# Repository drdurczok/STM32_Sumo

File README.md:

# STM32_Sumo
Sumo robot PCB based on STM32 and source code.

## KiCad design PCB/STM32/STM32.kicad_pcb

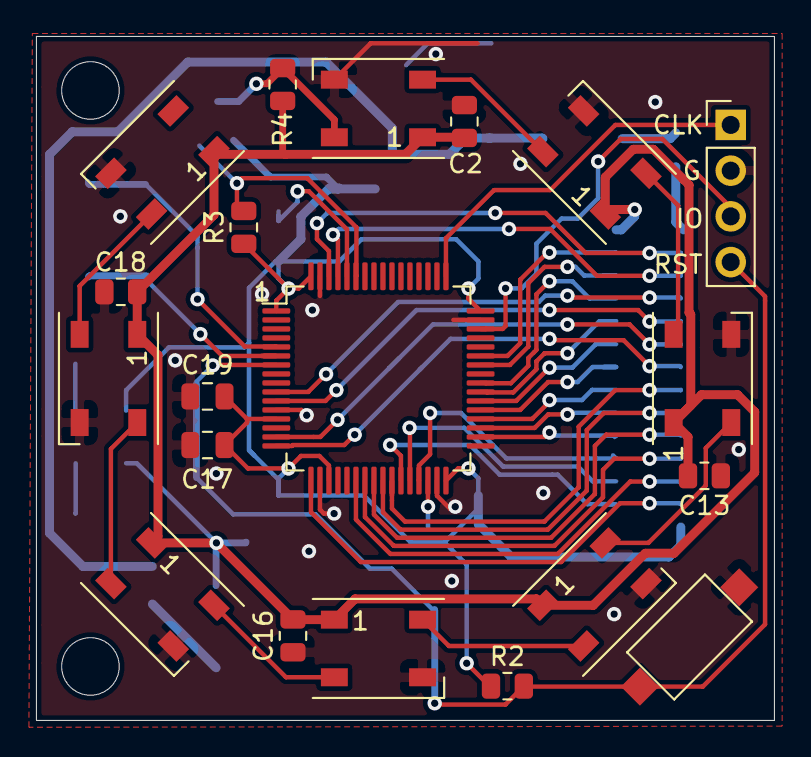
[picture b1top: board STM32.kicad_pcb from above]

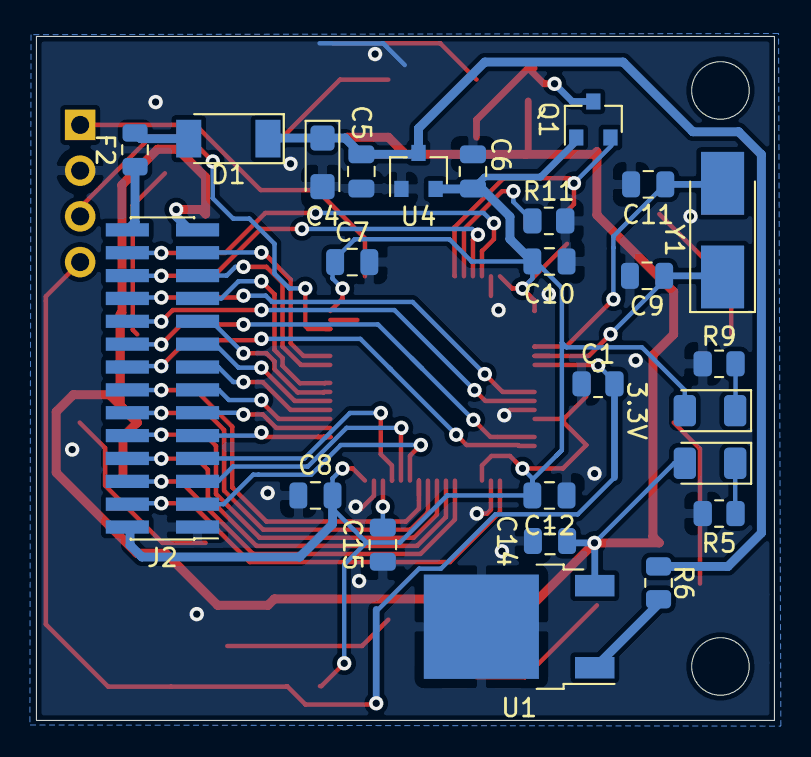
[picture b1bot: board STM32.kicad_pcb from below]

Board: 2 copper layers, 41.0 x 38.0 mm, 45 parts (25 on the bottom side), 49 nets.

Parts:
C1, C2, C13, C16, C18: 100nF; R_0805_2012Metric
C4: 10uF; CP_EIA-3216-18_Kemet-A
C5, C6: 4.7uF; C_0805_2012Metric
C7, C8, C10, C12, C14, C19: 100nF; C_0805_2012Metric
C9, C11: 20pF; C_0805_2012Metric
C15: 2.2uF; C_0805_2012Metric
C17: 1uF; C_0805_2012Metric
D1: Schottky; D_SOD-128
D2, D11: Power_On; LED_1206_3216Metric
D3, D4, D5, D6, D7, D8, D9, D10: WS2812B; LED_WS2812B_PLCC4_5.0x5.0mm_P3.2mm
F2: Fuse; Fuse_0805_2012Metric
J2: St-Link; PinHeader_2x14_P1.27mm_Vertical_SMD
J18: St-Link; PinHeader_1x04_P2.54mm_Vertical
Q1: BSS138; SOT-23
R2: 100k; R_0805_2012Metric
R3, R4: 10K; R_0805_2012Metric
R5, R9: RLed; R_0805_2012Metric
R6: 0R; R_0805_2012Metric
R11: 100K; R_0805_2012Metric
SW1: SW_Push; SW_SPST_CK_RS282G05A3
U1: L7805; TO-252-2
U3: STM32F411RETx; LQFP-64_10x10mm_P0.5mm
U4: MCP1703A-3302_SOT23; SOT-23
Y1: 16MHz; Crystal_SMD_5032-2Pin_5.0x3.2mm_HandSoldering

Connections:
+3V3: C6.1, C7.2, C8.2, C10.1, C12.2, C17.2, C19.1, D2.2, J2.2, Q1.1, R2.1, R3.1, U3.1, U3.13, U3.19, U3.32, U3.48, U3.64, U4.2
+5V: C2.2, C13.2, C14.1, C16.2, C18.2, D3.1, D4.1, D5.1, D6.1, D7.1, D8.1, D9.1, D10.1, D11.2, J2.27, R4.2, U1.3
GND: C1.1, C2.1, C4.2, C5.2, C6.2, C7.1, C8.1, C9.2, C10.2, C11.2, C12.1, C13.1, C14.2, C15.1, C16.1, C17.1, C18.1, C19.2, D3.3, D4.3, D5.3, D6.3, D7.3, D8.3, D9.3, D10.3, J2.1, J18.2, R5.2, R9.2, R11.1, SW1.2, U1.2, U3.12, U3.18, U3.31, U3.47, U3.63, U4.1
LED: D3.4, Q1.3, R4.1
unnamed: C9.1, U3.6, Y1.1
unnamed: C11.1, U3.5, Y1.2
unnamed: C15.2, U3.30
unnamed: D1.2, F2.2
unnamed: D2.1, R9.1
unnamed: D3.2, D4.4
unnamed: D4.2, D5.4
unnamed: D5.2, D6.4
unnamed: D6.2, D7.4
unnamed: D7.2, D8.4
unnamed: D8.2, D9.4
unnamed: D9.2, D10.4
unnamed: D11.1, R5.1
unnamed: R6.1, U1.1
unnamed: R11.2, U3.60
PA1: J2.18, U3.15
PA2: J2.16, U3.16
PA3: J2.4, U3.17
PA6: J2.6, U3.22
PA7: J2.8, U3.23
PA9: J2.23, U3.42
PA10: J2.25, U3.43
PB0: J2.14, U3.26
PB1: J2.3, U3.27
PB2: J2.5, U3.28
PB7: Q1.2, R3.2, U3.59
PB8: J2.24, U3.61
PB9: J2.26, U3.62
PB10: J2.7, U3.29
PB13: J2.9, U3.34
PB14: J2.11, U3.35
PB15: J2.13, U3.36
PC2: J2.22, U3.10
PC3: J2.20, U3.11
PC4: J2.10, U3.24
PC5: J2.12, U3.25
PC6: J2.15, U3.37
PC7: J2.17, U3.38
PC8: J2.19, U3.39
PC9: J2.21, U3.40
RESET: C1.2, J18.4, R2.2, SW1.1, U3.7
SWD_CLK: J18.1, U3.49
SWD_IO: J18.3, U3.46
VPP: F2.1, J2.28
V_Stable: C4.1, C5.1, D1.1, R6.2, U4.3

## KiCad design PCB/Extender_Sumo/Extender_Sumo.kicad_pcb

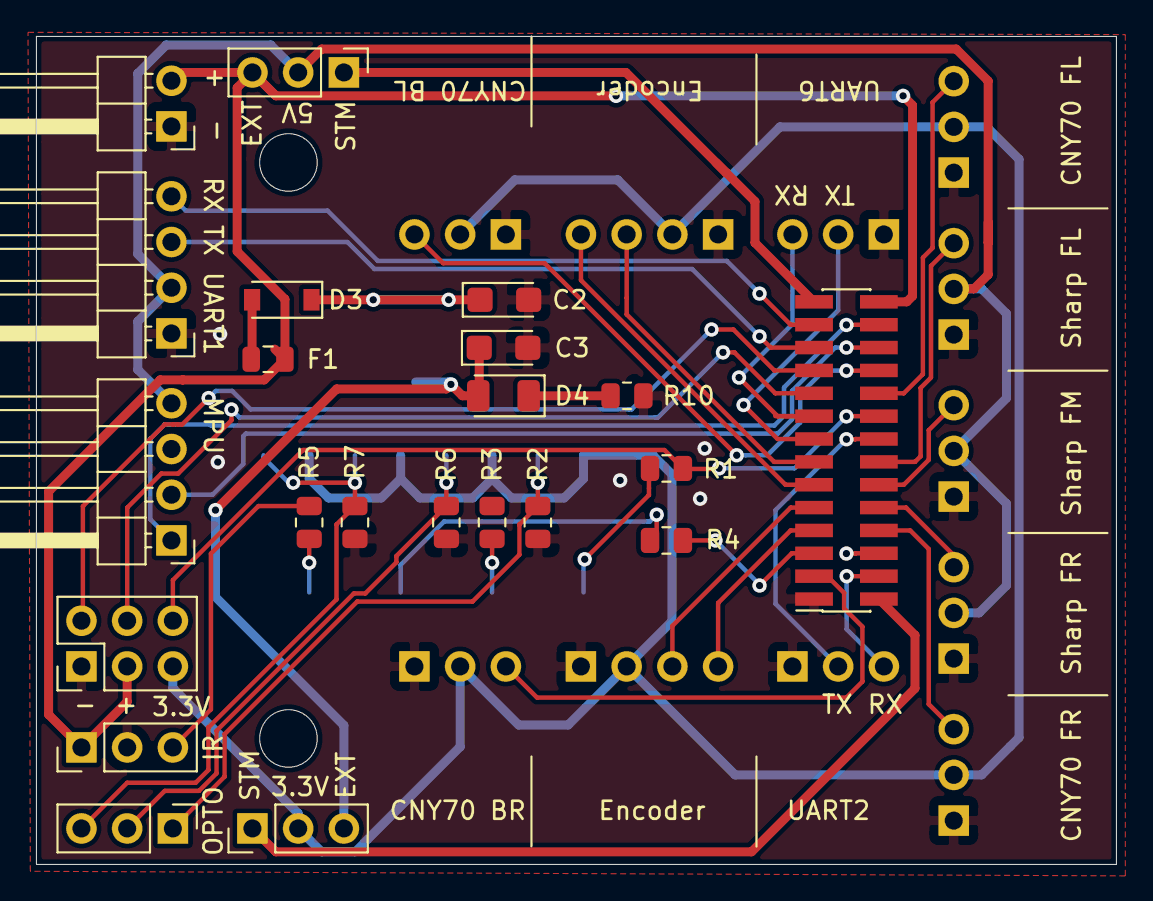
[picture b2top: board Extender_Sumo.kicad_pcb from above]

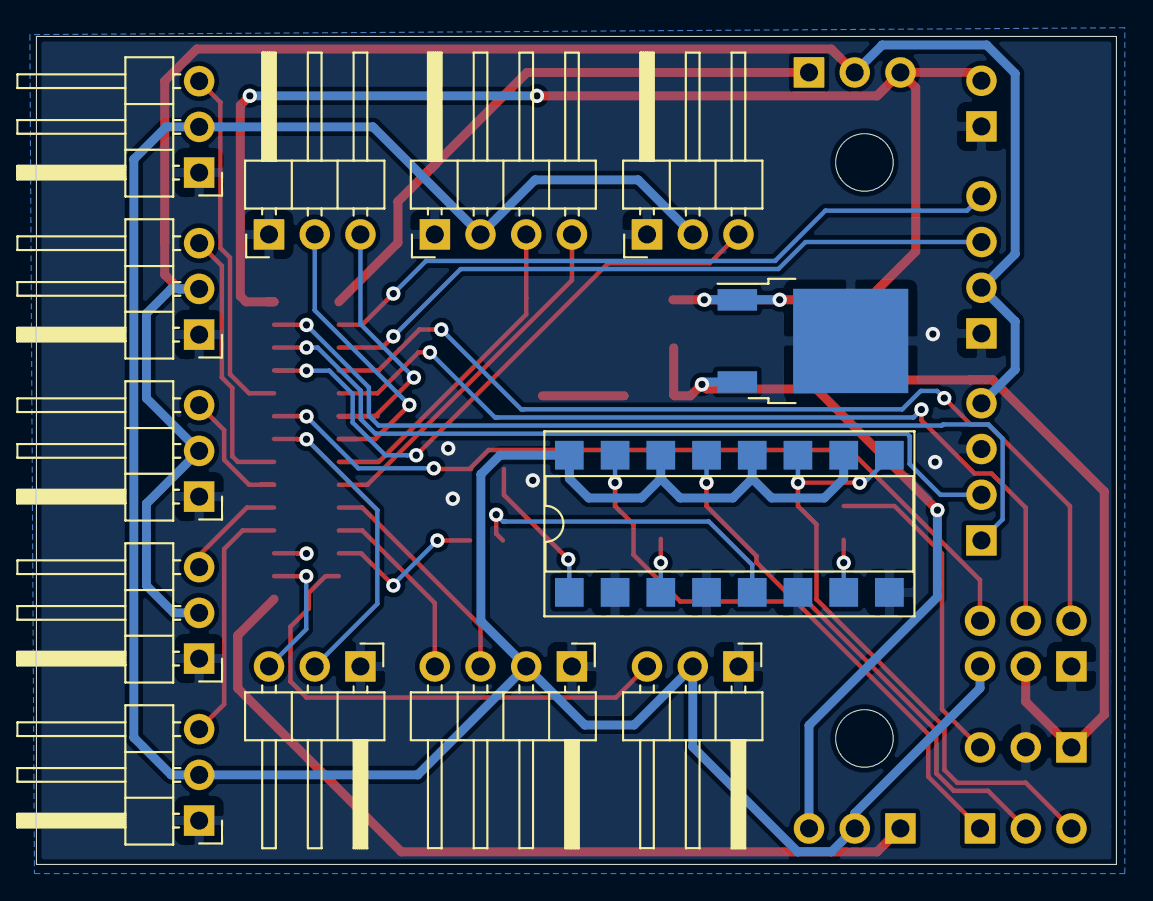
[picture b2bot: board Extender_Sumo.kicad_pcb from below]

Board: 2 copper layers, 60.0 x 46.0 mm, 35 parts (13 on the bottom side), 41 nets.

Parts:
C2, C3: 10uf; CP_EIA-3216-18_Kemet-A
D3: Schottky; D_SOD-123
D4: Power_On; LED_1206_3216Metric
F1: Fuse; Fuse_0805_2012Metric
J1: CNY70 FR; PinHeader_1x03_P2.54mm_Horizontal
J2: CNY70 FL; PinHeader_1x03_P2.54mm_Horizontal
J3: Sharp FL; PinHeader_1x03_P2.54mm_Horizontal
J4: Sharp FM; PinHeader_1x03_P2.54mm_Horizontal
J5: Sharp FR; PinHeader_1x03_P2.54mm_Horizontal
J6: Right Driver; PinHeader_1x03_P2.54mm_Horizontal
J7: Left Driver; PinHeader_1x03_P2.54mm_Horizontal
J8: Right Encoder; PinHeader_1x04_P2.54mm_Horizontal
J9: CNY70 BR; PinHeader_1x03_P2.54mm_Horizontal
J10: CNY70 BL; PinHeader_1x03_P2.54mm_Horizontal
J11: Left Encoder; PinHeader_1x04_P2.54mm_Horizontal
J12: Extra Pins; PinHeader_2x03_P2.54mm_Vertical
J13: Conn_02x14_Odd_Even; PinSocket_2x14_P1.27mm_Vertical_SMD
J14: IR Module; PinHeader_1x03_P2.54mm_Vertical
J15: Bluetooth; PinHeader_1x04_P2.54mm_Horizontal
J16: Optocoupler Out; PinHeader_1x03_P2.54mm_Vertical
J17: MPU6050 I2C; PinHeader_1x04_P2.54mm_Horizontal
J18, J19: Conn_01x03; PinHeader_1x03_P2.54mm_Vertical
J20: Conn_01x02; PinHeader_1x02_P2.54mm_Horizontal
R1, R3, R4, R5: 330R; R_0805_2012Metric
R2, R6, R7: 10K; R_0805_2012Metric
R10: RLed; R_0805_2012Metric
U1: LF33_TO252; TO-252-2
U2: LTV-847; DIP-16_W7.62mm_SMDSocket_SmallPads

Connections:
3.3V_1A: C3.1, D4.2, J18.3, U1.3
3.3V_STM: J13.2, J18.1
5V_STM: J13.27, J19.1
+3V3: J1.2, J2.2, J8.2, J9.2, J10.2, J11.2, J12.5, J18.2, U2.10, U2.12, U2.14, U2.16
+5V: J3.2, J4.2, J5.2, J15.2, J17.4, J19.2
GND: C2.2, C3.2, J1.1, J2.1, J3.1, J4.1, J5.1, J6.1, J7.1, J8.1, J9.1, J10.1, J11.1, J12.1, J13.1, J14.2, J15.1, J17.3, J20.1, R2.2, R6.2, R7.2, R10.1, U1.2, U2.2, U2.4, U2.6, U2.8
unnamed: C2.1, D3.1, U1.1
unnamed: D3.2, F1.2
unnamed: D4.1, R10.2
unnamed: J14.3, R5.2
unnamed: J16.1, R2.1, U2.15
unnamed: J16.2, R6.1, U2.13
unnamed: J16.3, R7.1, U2.9, U2.11
unnamed: R1.1, U2.1
unnamed: R3.1, U2.3
unnamed: R4.1, U2.5
unnamed: R5.1, U2.7
PA1: J12.6, J13.18, R1.2
PA2: J6.2, J13.16
PA3: J6.3, J13.4
PA7: J1.3, J13.8
PA9: J13.23, J15.3
PA10: J13.25, J15.4
PB0: J3.3, J13.14
PB1: J9.3, J13.3
PB2: J13.5, R4.2
PB8: J13.24, J17.2
PB9: J13.26, J17.1
PB10: J8.4, J13.7
PB13: J8.3, J13.9
PB14: J11.4, J13.11
PB15: J11.3, J13.13
PC2: J10.3, J13.22
PC3: J2.3, J13.20
PC4: J5.3, J13.10
PC5: J4.3, J13.12
PC6: J7.2, J13.15
PC7: J7.3, J13.17
PC8: J12.4, J13.19
PC9: J12.2, J13.21
VPP: F1.1, J12.3, J13.28, J14.1, J19.3, J20.2

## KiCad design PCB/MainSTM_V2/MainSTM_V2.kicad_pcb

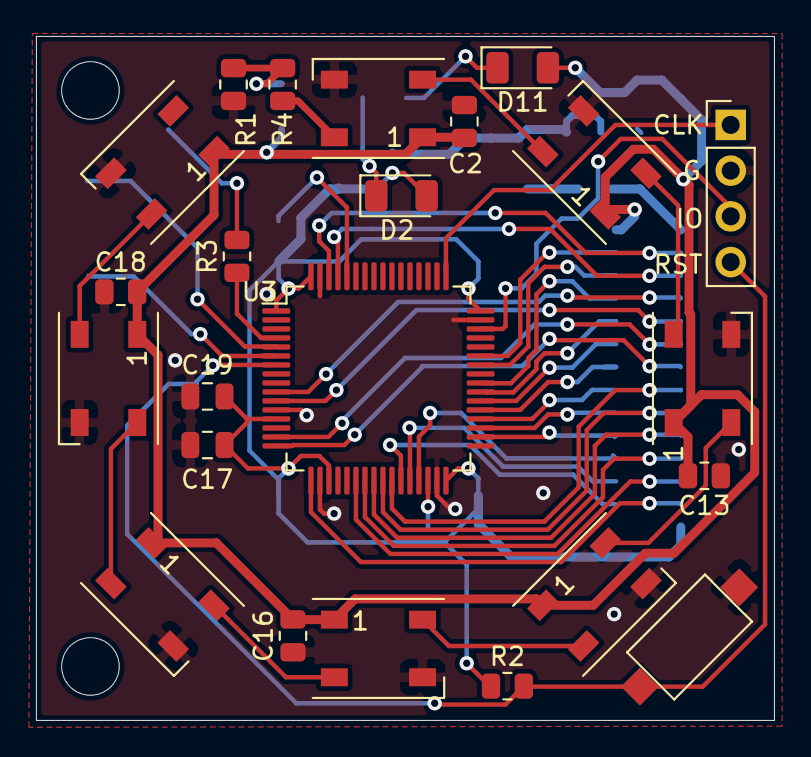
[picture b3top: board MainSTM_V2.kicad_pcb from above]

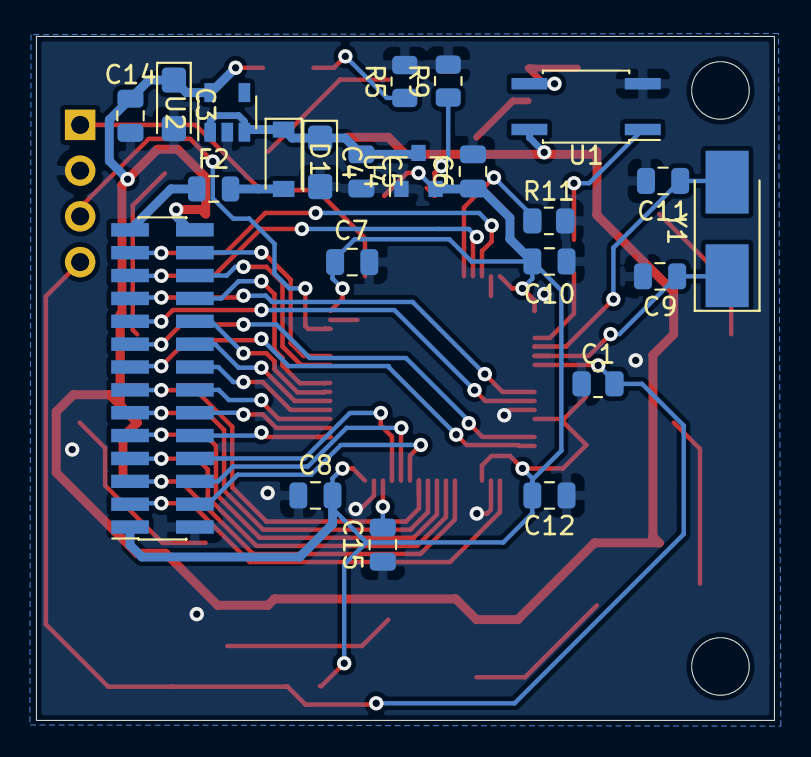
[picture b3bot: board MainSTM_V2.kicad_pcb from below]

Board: 2 copper layers, 41.0 x 38.0 mm, 46 parts (23 on the bottom side), 50 nets.

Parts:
C1, C2, C13, C16, C18: 100nF; R_0805_2012Metric
C3, C4: 10uF; CP_EIA-3216-18_Kemet-A
C5, C6: 4.7uF; C_0805_2012Metric
C7, C8, C10, C12, C14, C19: 100nF; C_0805_2012Metric
C9, C11: 20pF; C_0805_2012Metric
C15: 2.2uF; C_0805_2012Metric
C17: 1uF; C_0805_2012Metric
CLK: St-Link; PinHeader_1x04_P2.54mm_Vertical
D1: Schottky; D_SOD-123
D2, D11: Power_On; LED_1206_3216Metric
D3, D4, D5, D6, D7, D8, D9, D10: WS2812B; LED_WS2812B_PLCC4_5.0x5.0mm_P3.2mm
F2: Fuse; Fuse_0805_2012Metric
J2: St-Link; PinSocket_2x14_P1.27mm_Vertical_SMD
R1: 10k; R_0805_2012Metric
R2: 100k; R_0805_2012Metric
R3: 220R; R_0805_2012Metric
R4: 0R; R_0805_2012Metric
R5, R9: RLed; R_0805_2012Metric
R11: 100K; R_0805_2012Metric
SW1: SW_Push; SW_SPST_CK_RS282G05A3
U1: LTV-356T; SO-4_4.4x3.6mm_P2.54mm
U2: MIC5205-5.0YM5; SOT-23-5
U3: STM32F411RETx; LQFP-64_10x10mm_P0.5mm
U4: MCP1703A-3302_SOT23; SOT-23
Y1: 16MHz; Crystal_SMD_5032-2Pin_5.0x3.2mm_HandSoldering

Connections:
+3V3: C6.1, C7.2, C8.2, C10.1, C12.2, C17.2, C19.1, D2.2, J2.1, R2.1, U3.1, U3.13, U3.19, U3.32, U3.48, U3.64, U4.2
+5V: C2.2, C3.1, C13.2, C14.1, C16.2, C18.2, D3.1, D4.1, D5.1, D6.1, D7.1, D8.1, D9.1, D10.1, D11.2, J2.28, U1.4, U2.5
GND: C1.1, C2.1, C3.2, C4.2, C5.2, C6.2, C7.1, C8.1, C9.2, C10.2, C11.2, C12.1, C13.1, C14.2, C15.1, C16.1, C17.1, C18.1, C19.2, CLK.2, D3.3, D4.3, D5.3, D6.3, D7.3, D8.3, D9.3, D10.3, J2.2, R1.2, R5.2, R9.2, R11.1, SW1.2, U1.2, U2.2, U3.12, U3.18, U3.31, U3.47, U3.63, U4.1
LED: D3.4, R4.2
unnamed: C9.1, U3.6, Y1.1
unnamed: C11.1, U3.5, Y1.2
unnamed: C15.2, U3.30
unnamed: D1.2, F2.2
unnamed: D2.1, R9.1
unnamed: D3.2, D4.4
unnamed: D4.2, D5.4
unnamed: D5.2, D6.4
unnamed: D6.2, D7.4
unnamed: D7.2, D8.4
unnamed: D8.2, D9.4
unnamed: D9.2, D10.4
unnamed: D11.1, R5.1
unnamed: R1.1, R4.1, U1.3
unnamed: R3.2, U1.1
unnamed: R11.2, U3.60
PA1: J2.17, U3.15
PA2: J2.15, U3.16
PA3: J2.3, U3.17
PA6: J2.5, U3.22
PA7: J2.7, U3.23
PA9: J2.24, U3.42
PA10: J2.26, U3.43
PB0: J2.13, U3.26
PB1: J2.4, U3.27
PB2: J2.6, U3.28
PB8: J2.23, U3.61
PB9: J2.25, U3.62
PB10: J2.8, U3.29
PB13: J2.10, U3.34
PB14: J2.12, U3.35
PB15: J2.14, U3.36
PC2: J2.21, U3.10
PC3: J2.19, U3.11
PC4: J2.9, U3.24
PC5: J2.11, U3.25
PC6: J2.16, U3.37
PC7: J2.18, U3.38
PC8: J2.20, U3.39
PC9: J2.22, U3.40
PC15: R3.1, U3.4
RESET: C1.2, CLK.4, R2.2, SW1.1, U3.7
SWD_CLK: CLK.1, U3.49
SWD_IO: CLK.3, U3.46
VPP: F2.1, J2.27
V_Stable: C4.1, C5.1, D1.1, U2.1, U2.3, U4.3

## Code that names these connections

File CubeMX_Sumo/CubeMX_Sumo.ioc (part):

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Mcu.Name=STM32F411R(C-E)Tx
Mcu.Package=LQFP64
Mcu.UserName=STM32F411RETx
PA10.Mode=Asynchronous
PA10.Signal=USART1_RX
PA2.Mode=Asynchronous
PA2.Signal=USART2_TX
PA3.Mode=Asynchronous
PA3.Signal=USART2_RX
PA6.GPIOParameters=GPIO_Label
PA6.GPIO_Label=Sharp RM
PA6.Signal=ADCx_IN6
PA7.GPIOParameters=GPIO_Label
PA7.GPIO_Label=CNY70 FR
PA7.Signal=ADCx_IN7
PA9.Mode=Asynchronous
PA9.Signal=USART1_TX
PB0.GPIOParameters=GPIO_Label
PB0.GPIO_Label=Sharp FL
PB0.Signal=ADCx_IN8
PB1.GPIOParameters=GPIO_Label
PB1.GPIO_Label=CNY70 RR
PB1.Signal=ADCx_IN9
PC0.GPIOParameters=GPIO_Label
PC0.GPIO_Label=NeoPixel
PC0.Signal=GPIO_Output
PC2.GPIOParameters=GPIO_Label
PC2.GPIO_Label=CNY70 RL
PC2.Signal=ADCx_IN12
PC3.GPIOParameters=GPIO_Label
PC3.GPIO_Label=CNY70 FL
PC3.Signal=ADCx_IN13
PC4.GPIOParameters=GPIO_Label
PC4.GPIO_Label=Sharp FR
PC4.Signal=ADCx_IN14
PC5.GPIOParameters=GPIO_Label
PC5.GPIO_Label=Sharp FM
PC5.Signal=ADCx_IN15
PC6.Mode=Asynchronous
PC6.Signal=USART6_TX
PC7.Mode=Asynchronous
PC7.Signal=USART6_RX
RCC.HSE_VALUE=25000000
RCC.SYSCLKFreq_VALUE=84000000
RCC.SYSCLKSource=RCC_SYSCLKSOURCE_PLLCLK
board=custom

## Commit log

2020-12-30 Minimum STM32 startup
    Minimum code required to startup STM32 controller
2020-12-30 Minimum STM32 program based on CubeMx
    Blinking LED on PA5
2020-12-30 File Structure Update
2020-12-31 File Restructuring
    Seperated CodeMX from src code
2020-12-31 Added C++ Compiling
2020-12-31 Added handlers file for STM32
2020-12-31 Added UART support
    Code still contains tests - should be moved to diagnostics
2021-01-01 KiCad STM32 PCB and documentation
2021-01-02 STM32 PCB update + BOM
2021-01-03 New Extender PCB + STM32 PCB Update
2021-01-04 Added mounting holes
2021-02-05 Changed NeoPixel output pin
2021-02-05 Changed NeoPixel output pin - fix
2021-02-07 WS1812B Working Update
    Added WS2812B libraries.
    Added WS2812B pin to CubeMX.
    Fixed PCB errors with WS2812B.
    TODO:
    Replace LTV-356 with faster chip
    MIC5205 needs to be replaced for higher power
2021-02-12 Added bi-directional level shifter
    Replaced to newer level shifter for WS2812B
2021-02-12 Replaced 5V Power Regulator
2021-02-15 ADC DMA
2021-03-07 Fixed ADC Channel
2021-06-12 Opponent Detection Class added
    Added new opponent detection files.
    UART1 output for opponent detection.
2021-06-16 Opponent distance and angle detection
    Implemented basic opponent distance and angle calculation based on Sharp sensor data.
2021-09-27 Added robot wiring diagram
2022-01-15 Project Migration to CUBEIDE
